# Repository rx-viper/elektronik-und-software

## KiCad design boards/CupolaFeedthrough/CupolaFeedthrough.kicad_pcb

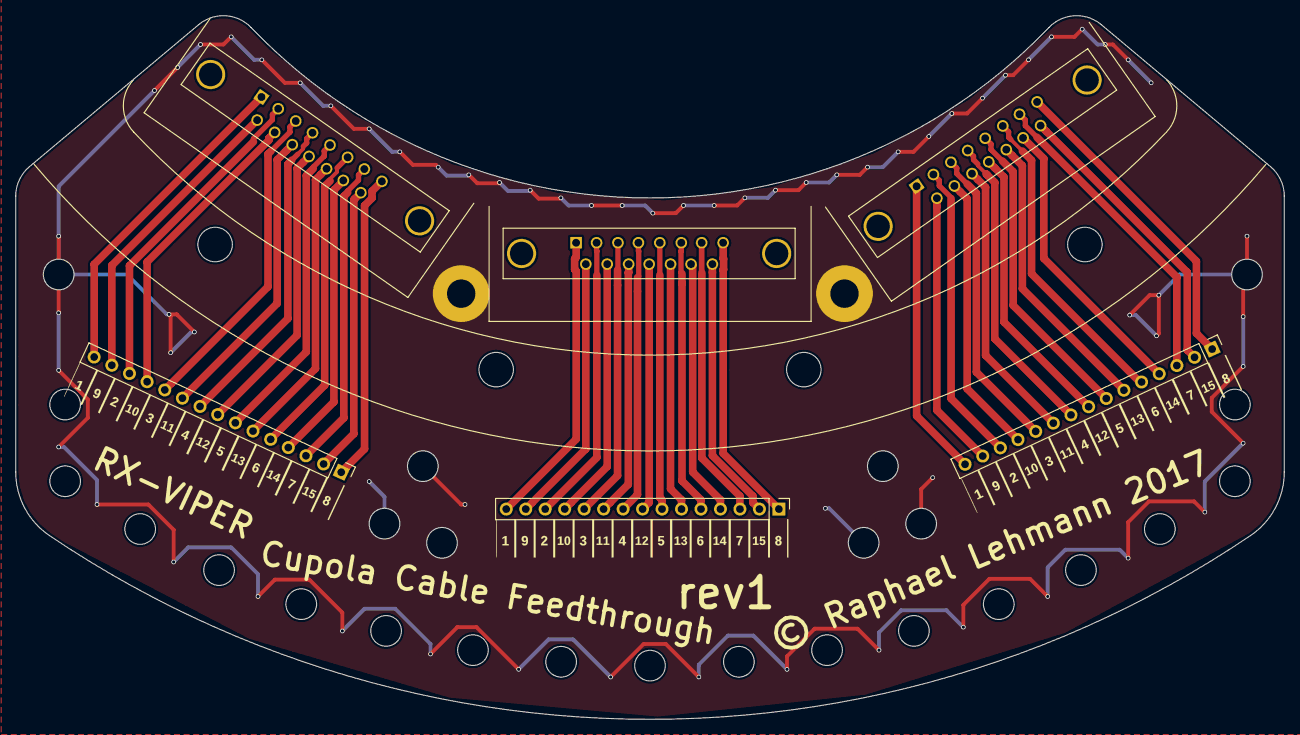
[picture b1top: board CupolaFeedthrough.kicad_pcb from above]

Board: 2 copper layers, 165.5 x 91.8 mm, 16 parts (0 on the bottom side), 46 nets.

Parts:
J101, J102, J103: CONN_01X15; Pin_Header_Straight_1x15_Pitch2.54mm
J104, J105, J106: DB15_FEMALE; DB15MD
J107, J108, J109, J110, J120, J121, J130, J131: GND; MountingHole_4mm
J136, J136#2: GND; MountingHole_3.7mm_Pad

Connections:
GND: J107.1, J108.1, J109.1, J110.1, J120.1, J121.1, J130.1, J131.1, J136.1, J136#2.1
unnamed: J101.1, J104.8
unnamed: J101.2, J104.15
unnamed: J101.3, J104.7
unnamed: J101.4, J104.14
unnamed: J101.5, J104.6
unnamed: J101.6, J104.13
unnamed: J101.7, J104.5
unnamed: J101.8, J104.12
unnamed: J101.9, J104.4
unnamed: J101.10, J104.11
unnamed: J101.11, J104.3
unnamed: J101.12, J104.10
unnamed: J101.13, J104.2
unnamed: J101.14, J104.9
unnamed: J101.15, J104.1
unnamed: J102.1, J105.8
unnamed: J102.2, J105.15
unnamed: J102.3, J105.7
unnamed: J102.4, J105.14
unnamed: J102.5, J105.6
unnamed: J102.6, J105.13
unnamed: J102.7, J105.5
unnamed: J102.8, J105.12
unnamed: J102.9, J105.4
unnamed: J102.10, J105.11
unnamed: J102.11, J105.3
unnamed: J102.12, J105.10
unnamed: J102.13, J105.2
unnamed: J102.14, J105.9
unnamed: J102.15, J105.1
unnamed: J103.1, J106.8
unnamed: J103.2, J106.15
unnamed: J103.3, J106.7
unnamed: J103.4, J106.14
unnamed: J103.5, J106.6
unnamed: J103.6, J106.13
unnamed: J103.7, J106.5
unnamed: J103.8, J106.12
unnamed: J103.9, J106.4
unnamed: J103.10, J106.11
unnamed: J103.11, J106.3
unnamed: J103.12, J106.10
unnamed: J103.13, J106.2
unnamed: J103.14, J106.9
unnamed: J103.15, J106.1

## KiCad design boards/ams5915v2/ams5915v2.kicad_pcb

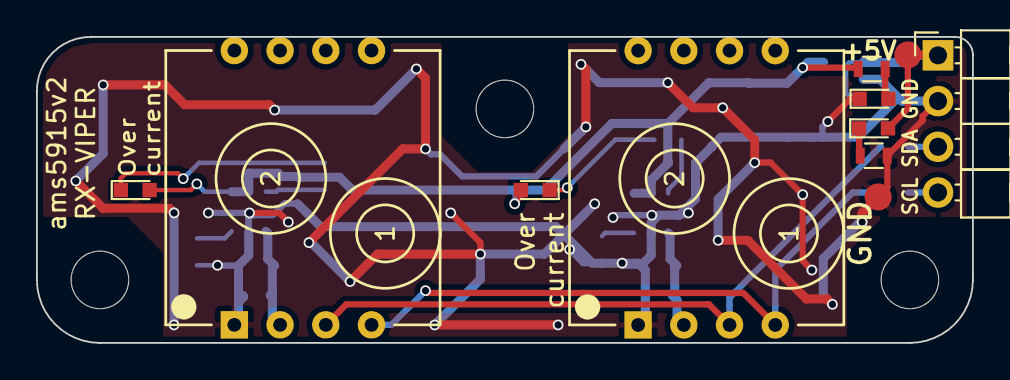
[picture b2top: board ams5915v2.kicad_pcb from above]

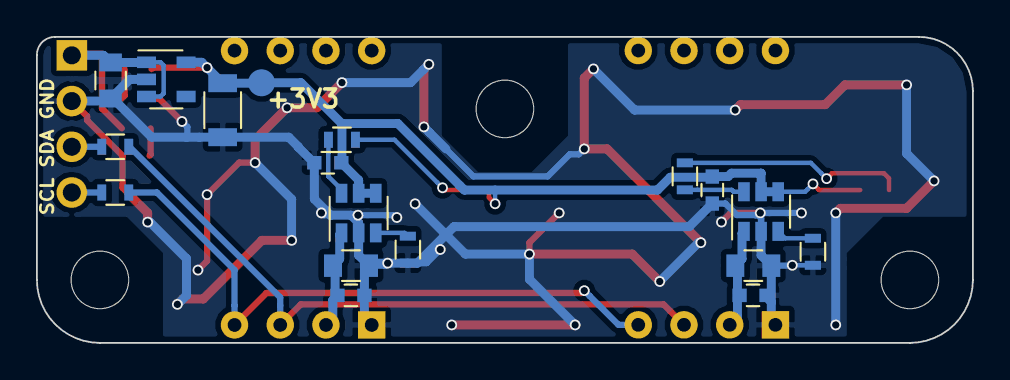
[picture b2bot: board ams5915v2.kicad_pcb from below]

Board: 2 copper layers, 52.0 x 17.0 mm, 29 parts (18 on the bottom side), 17 nets.

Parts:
C1, C7, C8: 1u; C_0805
C2: 10u; C_1206
C3, C4, C5, C6: 100n; C_0603
D1: LED_5v; LED_0603
D2: LED_3v3; LED_0603
D3: LED_P1; LED_0603
D4: LED_P2; LED_0603
J1: Conn_01x04; Pin_Header_Angled_1x04_Pitch2.54mm
R1, R2: 100; R_0603
R3: 4k7; R_0603
R4, R6, R8: 2k7; R_0603
R5, R7: 400k; R_0603
TP1: 5v; Measurement_Point_Round-SMD-Pad_Small
TP2: GND; Measurement_Point_Round-SMD-Pad_Small
TP3: 3v3; Measurement_Point_Round-SMD-Pad_Small
U1: TLV73333PDBVR; SOT-23-5
U2, U4: MAX4995A; SOT-23-6
U3, U5: AMS5915; AMS_5915-XXXX-D_differential_pressure_sensor

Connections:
+5V: C1.1, D1.2, J1.1, TP1.1, U1.1, U1.3
/3v3: C2.1, C3.1, C5.1, D3.2, D4.2, R4.1, TP3.1, U1.5, U2.4, U2.5, U4.4, U4.5
/SCL: J1.4, R1.1
/SDA: J1.3, R2.1
GND: C1.2, C2.2, C3.2, C4.2, C5.2, C6.2, C7.2, C8.2, D2.1, J1.2, R3.2, R5.1, R7.1, TP2.1, U1.2, U2.2, U3.1, U4.2, U5.1
unnamed: C4.1, C7.1, U2.1, U3.2
unnamed: C6.1, C8.1, U4.1, U5.2
unnamed: D1.1, R3.1
unnamed: D2.2, R4.2
unnamed: D3.1, R6.1
unnamed: D4.1, R8.1
unnamed: R1.2, U3.4, U5.4
unnamed: R2.2, U3.3, U5.3
unnamed: R5.2, U2.3
unnamed: R6.2, U2.6
unnamed: R7.2, U4.3
unnamed: R8.2, U4.6

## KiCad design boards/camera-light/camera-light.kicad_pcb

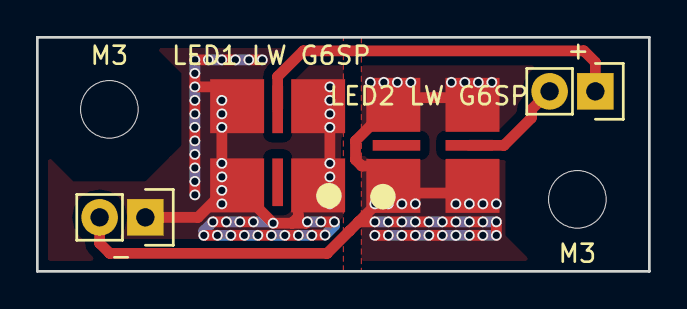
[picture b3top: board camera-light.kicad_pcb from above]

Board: 2 copper layers, 34.0 x 13.0 mm, 6 parts (0 on the bottom side), 4 nets.

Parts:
+: CONN_01X02; Pin_Header_Straight_1x02
-: CONN_01X02; Pin_Header_Straight_1x02
LED1 LW G6SP, LED2 LW G6SP: LED; LED_LW_G6SP
M3, M3#2: MountingHole_3.2mm_M3

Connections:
unnamed: +.1, LED1 LW G6SP.1
unnamed: -.1, LED1 LW G6SP.2, LED1 LW G6SP.~
unnamed: +.2, LED2 LW G6SP.1
unnamed: -.2, LED2 LW G6SP.2, LED2 LW G6SP.~

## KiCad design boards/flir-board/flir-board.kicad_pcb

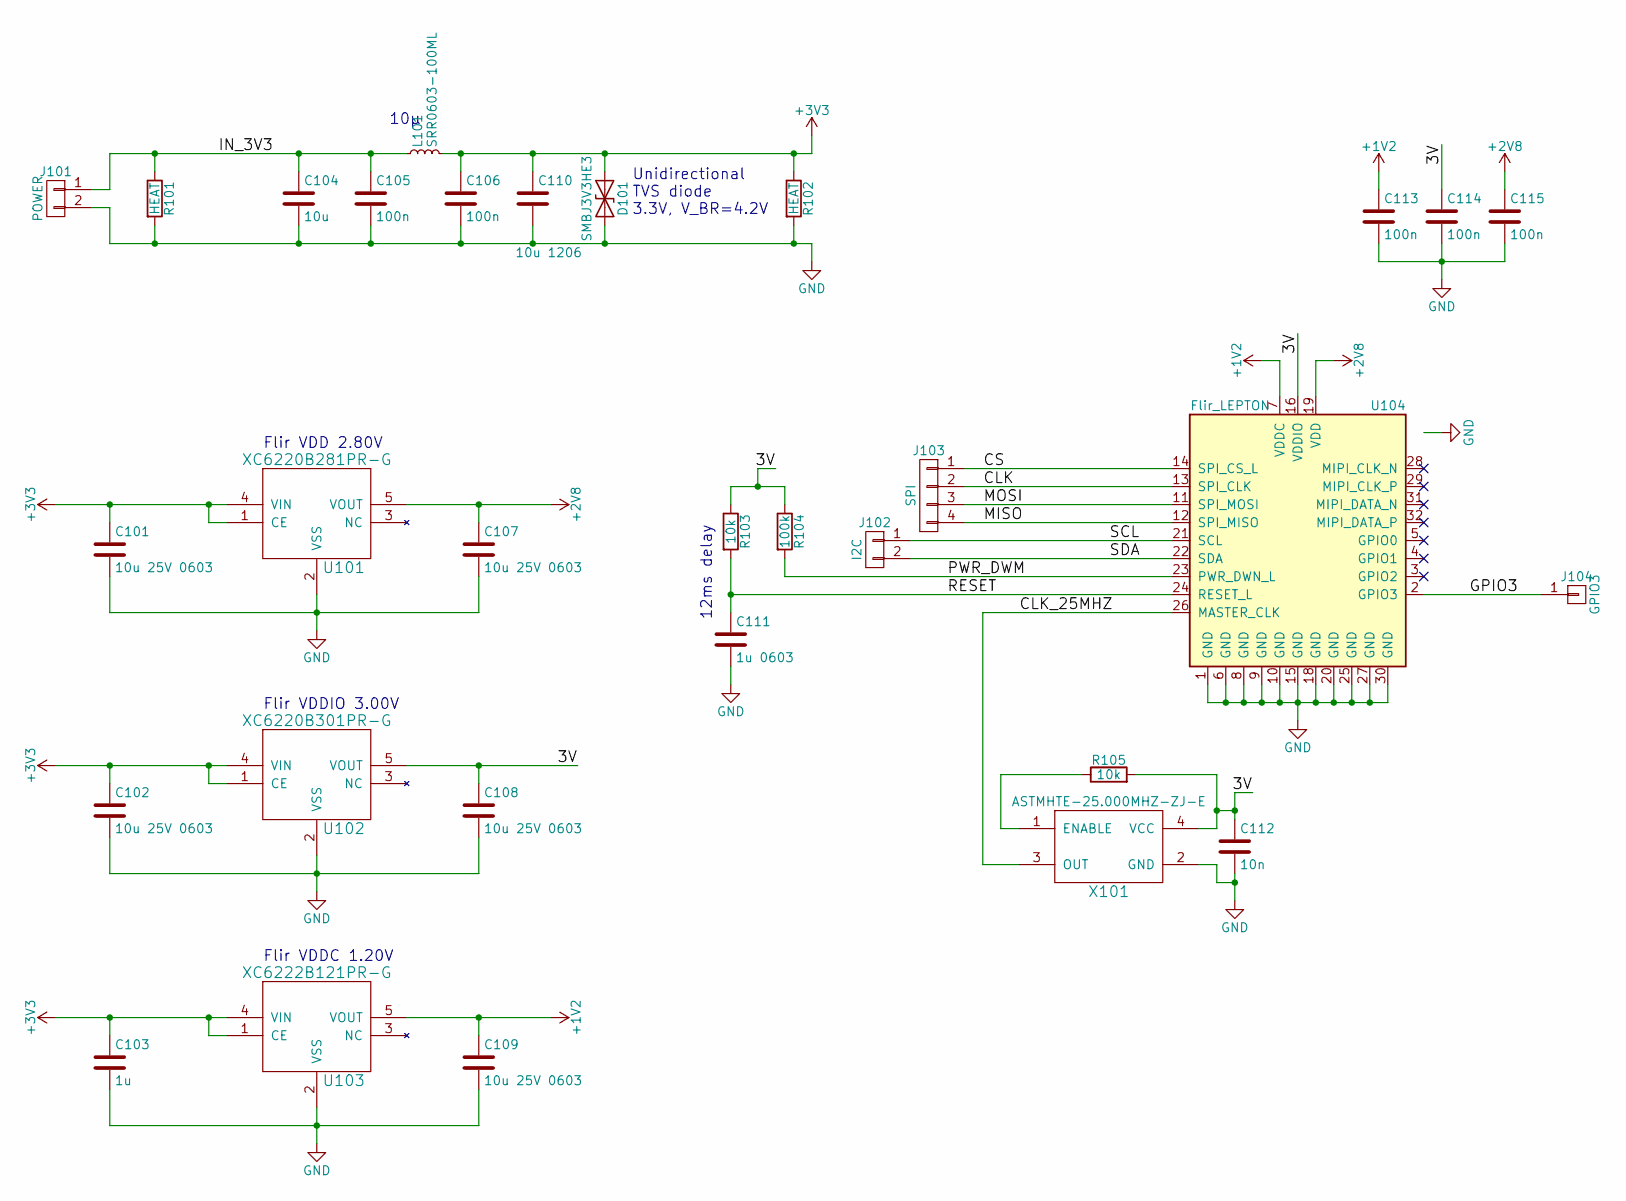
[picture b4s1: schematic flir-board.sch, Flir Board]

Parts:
C101, C102, C107, C108, C109: 10u 25V 0603; C_0603
C103: 1u; C_0603
C104: 10u; C_0805
C105, C106, C113, C114, C115: 100n; C_0603
C110: 10u 1206; C_1206
C111: 1u 0603; C_0603
C112: 10n; C_0603
D101: SMBJ3V3HE3; D_SMB_Standard
J101: POWER; Pin_Header_Straight_1x02_Pitch2.54mm
J102: I2C; Pin_Header_Straight_1x02_Pitch2.54mm
J103: SPI; Pin_Header_Straight_1x04_Pitch2.54mm
J104: GPIO3; Pin_Header_Straight_1x01_Pitch2.54mm
L101: SRR0603-100ML; L_7.3x7.3_H3.5
R101, R102: HEAT; R_1206
R103, R105: 10k; R_0603
R104: 100k; R_0603
U101: XC6220B281PR-G; SOT89-5_Housing
U102: XC6220B301PR-G; SOT89-5_Housing
U103: XC6222B121PR-G; SOT89-5_Housing
U104: Flir_LEPTON; Molex_105028-1001
X101: ASTMHTE-25.000MHZ-ZJ-E; ASTMHTE

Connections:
+1V2: C109.1, C113.1, U103.5 (VOUT), U104.7 (VDDC)
+2V8: C107.1, C115.1, U101.5 (VOUT), U104.19 (VDD)
+3V3: C101.1, C102.1, C103.1, C106.1, C110.1, D101.1 (A1), L101.2, R102.1, U101.1 (CE), U101.4 (VIN), U102.1 (CE), U102.4 (VIN), U103.1 (CE), U103.4 (VIN)
/3V: C108.1, C112.1, C114.1, R103.1, R104.1, R105.2, U102.5 (VOUT), U104.16 (VDDIO), X101.4 (VCC)
/CLK: J103.2, U104.13 (SPI_CLK)
/CLK_25MHZ: U104.26 (MASTER_CLK), X101.3 (OUT)
/CS: J103.1, U104.14 (SPI_CS_L)
/GPIO3: J104.1, U104.2 (GPIO3)
/IN_3V3: C104.1, C105.1, J101.1, L101.1, R101.1
/MISO: J103.4, U104.12 (SPI_MISO)
/MOSI: J103.3, U104.11 (SPI_MOSI)
/PWR_DWM: R104.2, U104.23 (PWR_DWN_L)
/RESET: C111.1, R103.2, U104.24 (RESET_L)
/SCL: J102.1, U104.21 (SCL)
/SDA: J102.2, U104.22 (SDA)
GND: C101.2, C102.2, C103.2, C104.2, C105.2, C106.2, C107.2, C108.2, C109.2, C110.2, C111.2, C112.2, C113.2, C114.2, C115.2, D101.2 (A2), J101.2, R101.2, R102.2, U101.2 (VSS), U102.2 (VSS), U103.2 (VSS), U104.1 (GND), U104.6 (GND), U104.8 (GND), U104.9 (GND), U104.10 (GND), U104.15 (GND), U104.18 (GND), U104.20 (GND), U104.25 (GND), U104.27 (GND), U104.30 (GND), U104.33, X101.2 (GND)
unnamed: R105.1, X101.1 (ENABLE)

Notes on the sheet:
Flir VDDIO 3.00V
Flir VDD 2.80V
Flir VDDC 1.20V
12ms delay
10µ
Unidirectional TVS diode 3.3V, V_BR=4.2V

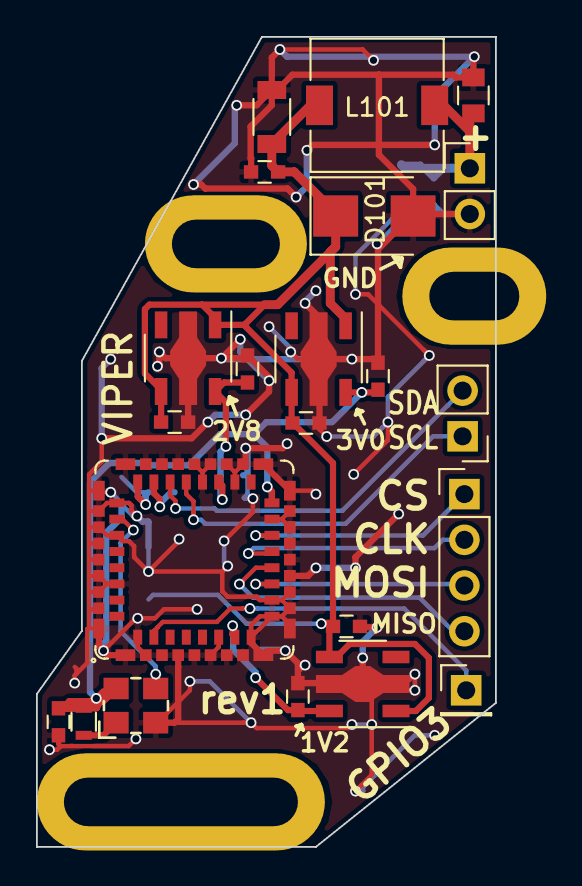
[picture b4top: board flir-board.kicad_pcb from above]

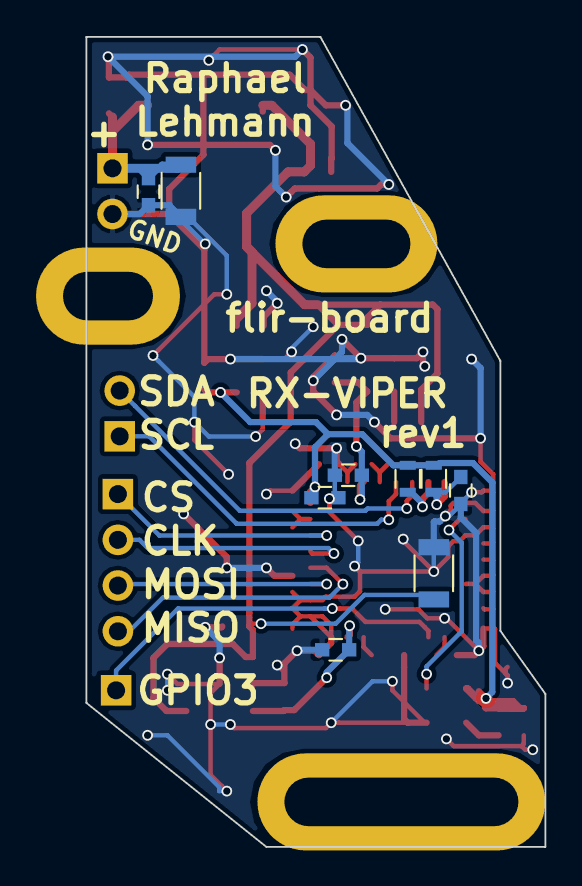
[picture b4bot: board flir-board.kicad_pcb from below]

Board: 2 copper layers, 25.5 x 45.0 mm, 31 parts (9 on the bottom side), 17 nets.

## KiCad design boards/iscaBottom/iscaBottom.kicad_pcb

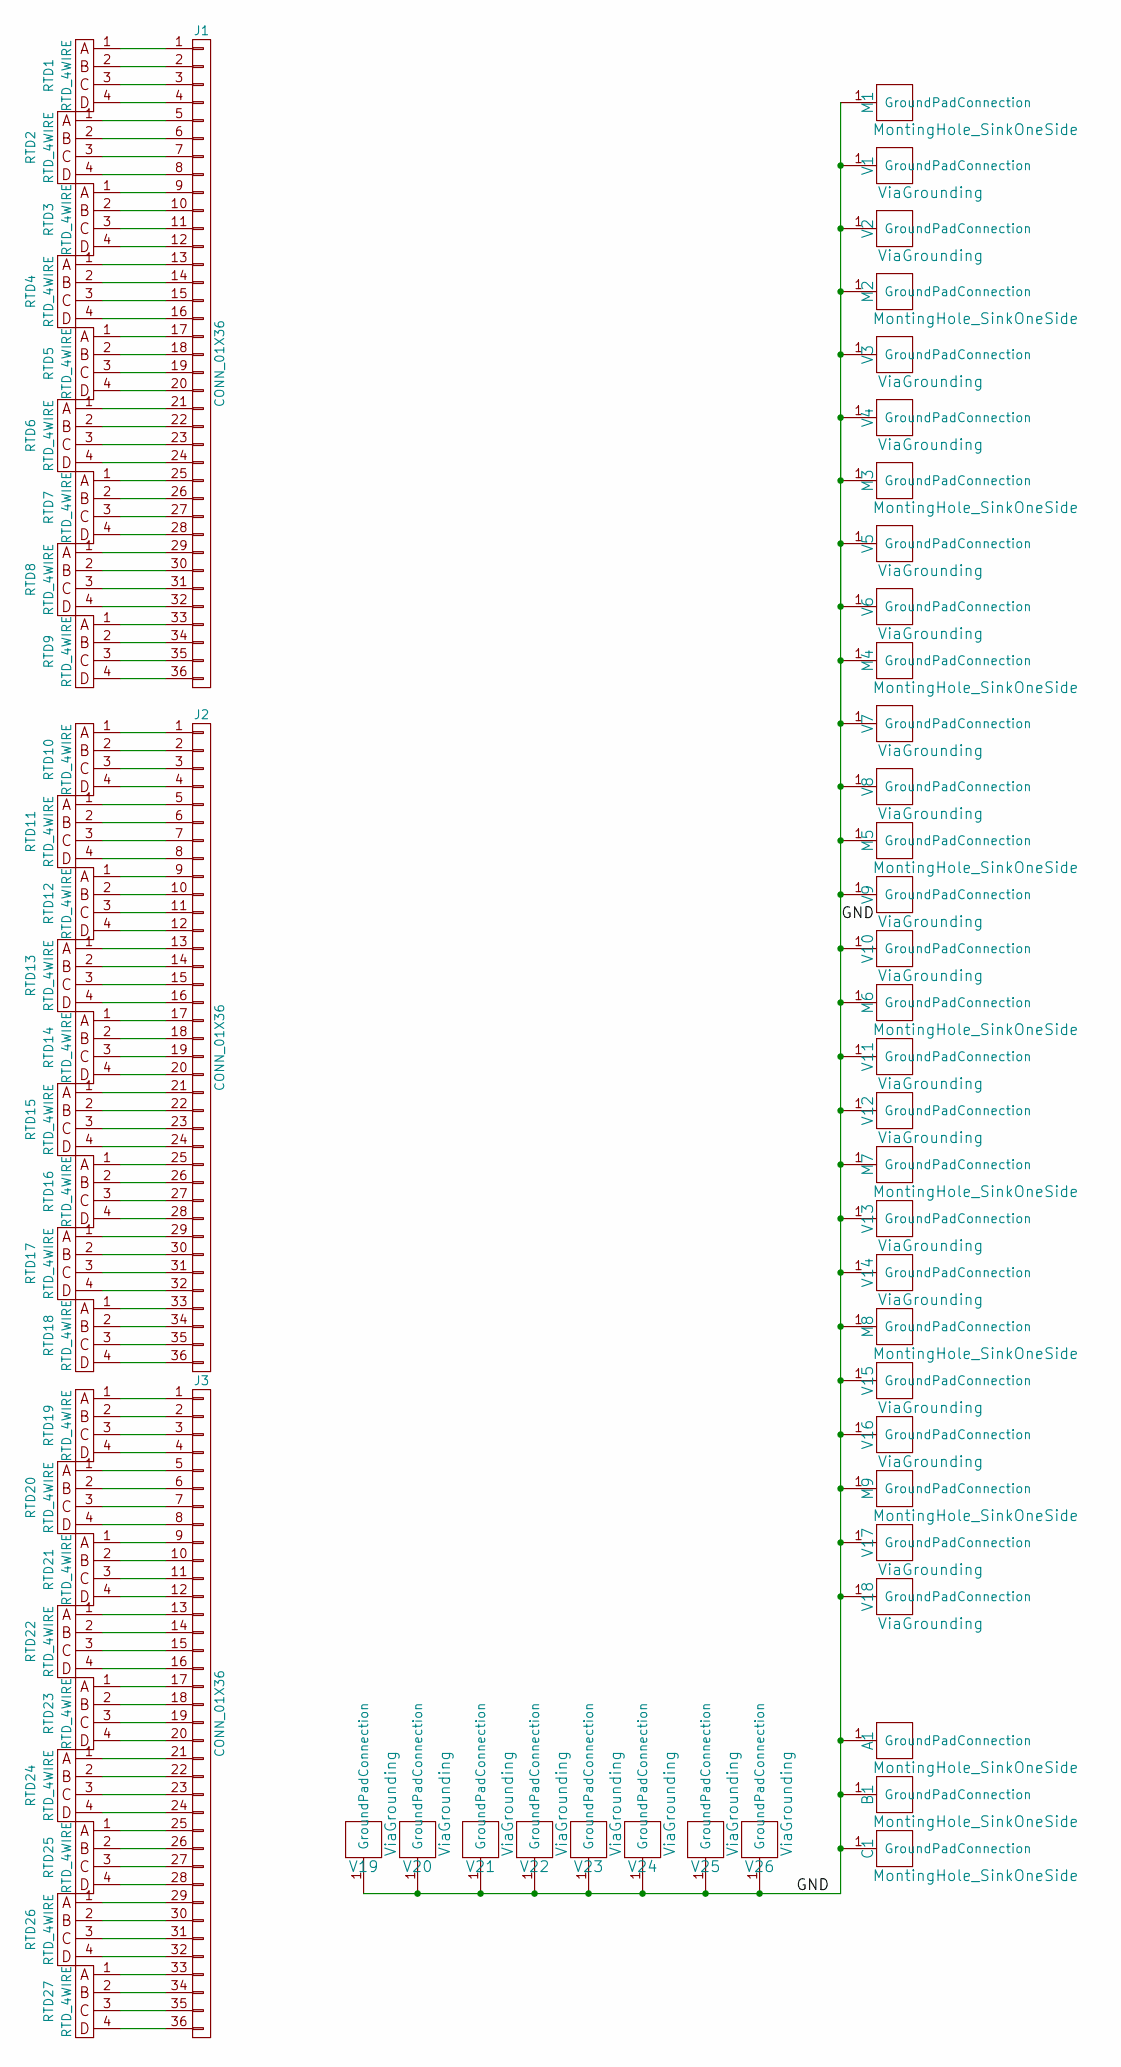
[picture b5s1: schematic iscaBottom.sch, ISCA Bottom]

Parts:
A1: MontingHole_SinkOneSide; MountingHoleM2_2.2mm_oneSided
B1: MontingHole_SinkOneSide; MountingHoleM2_2.2mm_oneSided
C1: MontingHole_SinkOneSide; MountingHoleM2_2.2mm_oneSided
J1, J2, J3: CONN_01X36; 36wire014mm2
M1, M2, M3, M4, M5, M6, M7, M8, M9: MontingHole_SinkOneSide; MountingHoleM2_2.2mm_oneSided
RTD1, RTD2, RTD3, RTD4, RTD5, RTD6, RTD7, RTD8, RTD9, RTD10, RTD11, RTD12, RTD13, RTD14, RTD19, RTD20, RTD21, RTD22, RTD23, RTD24, RTD25, RTD26, RTD27: RTD_4WIRE; 4wire_SMDsolder
RTD15, RTD16, RTD17, RTD18: RTD_4WIRE; 4wire_SMDsolder_reverse
V1, V2, V3, V4, V5, V6, V7, V8, V9, V10, V11, V12, V13, V14, V15, V16, V17, V18, V19, V20, V21, V22, V23, V24, V25, V26: ViaGrounding; GroundingVia

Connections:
/GND: A1.1, B1.1, C1.1, M1.1, M2.1, M3.1, M4.1, M5.1, M6.1, M7.1, M8.1, M9.1, V1.1, V2.1, V3.1, V4.1, V5.1, V6.1, V7.1, V8.1, V9.1, V10.1, V11.1, V12.1, V13.1, V14.1, V15.1, V16.1, V17.1, V18.1, V19.1, V20.1, V21.1, V22.1, V23.1, V24.1, V25.1, V26.1
unnamed: J1.1, RTD1.1
unnamed: J1.2, RTD1.2
unnamed: J1.3, RTD1.3
unnamed: J1.4, RTD1.4
unnamed: J1.5, RTD2.1
unnamed: J1.6, RTD2.2
unnamed: J1.7, RTD2.3
unnamed: J1.8, RTD2.4
unnamed: J1.9, RTD3.1
unnamed: J1.10, RTD3.2
unnamed: J1.11, RTD3.3
unnamed: J1.12, RTD3.4
unnamed: J1.13, RTD4.1
unnamed: J1.14, RTD4.2
unnamed: J1.15, RTD4.3
unnamed: J1.16, RTD4.4
unnamed: J1.17, RTD5.1
unnamed: J1.18, RTD5.2
unnamed: J1.19, RTD5.3
unnamed: J1.20, RTD5.4
unnamed: J1.21, RTD6.1
unnamed: J1.22, RTD6.2
unnamed: J1.23, RTD6.3
unnamed: J1.24, RTD6.4
unnamed: J1.25, RTD7.1
unnamed: J1.26, RTD7.2
unnamed: J1.27, RTD7.3
unnamed: J1.28, RTD7.4
unnamed: J1.29, RTD8.1
unnamed: J1.30, RTD8.2
unnamed: J1.31, RTD8.3
unnamed: J1.32, RTD8.4
unnamed: J1.33, RTD9.1
unnamed: J1.34, RTD9.2
unnamed: J1.35, RTD9.3
unnamed: J1.36, RTD9.4
unnamed: J2.1, RTD10.1
unnamed: J2.2, RTD10.2
unnamed: J2.3, RTD10.3
unnamed: J2.4, RTD10.4
unnamed: J2.5, RTD11.1
unnamed: J2.6, RTD11.2
unnamed: J2.7, RTD11.3
unnamed: J2.8, RTD11.4
unnamed: J2.9, RTD12.1
unnamed: J2.10, RTD12.2
unnamed: J2.11, RTD12.3
unnamed: J2.12, RTD12.4
unnamed: J2.13, RTD13.1
unnamed: J2.14, RTD13.2
unnamed: J2.15, RTD13.3
unnamed: J2.16, RTD13.4
unnamed: J2.17, RTD14.1
unnamed: J2.18, RTD14.2
unnamed: J2.19, RTD14.3
unnamed: J2.20, RTD14.4
unnamed: J2.21, RTD15.1
unnamed: J2.22, RTD15.2
unnamed: J2.23, RTD15.3
unnamed: J2.24, RTD15.4
unnamed: J2.25, RTD16.1
unnamed: J2.26, RTD16.2
unnamed: J2.27, RTD16.3
unnamed: J2.28, RTD16.4
unnamed: J2.29, RTD17.1
unnamed: J2.30, RTD17.2
unnamed: J2.31, RTD17.3
unnamed: J2.32, RTD17.4
unnamed: J2.33, RTD18.1
unnamed: J2.34, RTD18.2
unnamed: J2.35, RTD18.3
unnamed: J2.36, RTD18.4
unnamed: J3.1, RTD19.1
unnamed: J3.2, RTD19.2
unnamed: J3.3, RTD19.3
unnamed: J3.4, RTD19.4
unnamed: J3.5, RTD20.1
unnamed: J3.6, RTD20.2
unnamed: J3.7, RTD20.3
unnamed: J3.8, RTD20.4
unnamed: J3.9, RTD21.1
unnamed: J3.10, RTD21.2
unnamed: J3.11, RTD21.3
unnamed: J3.12, RTD21.4
unnamed: J3.13, RTD22.1
unnamed: J3.14, RTD22.2
unnamed: J3.15, RTD22.3
unnamed: J3.16, RTD22.4
unnamed: J3.17, RTD23.1
unnamed: J3.18, RTD23.2
unnamed: J3.19, RTD23.3
unnamed: J3.20, RTD23.4
unnamed: J3.21, RTD24.1
unnamed: J3.22, RTD24.2
unnamed: J3.23, RTD24.3
unnamed: J3.24, RTD24.4
unnamed: J3.25, RTD25.1
unnamed: J3.26, RTD25.2
unnamed: J3.27, RTD25.3
unnamed: J3.28, RTD25.4
unnamed: J3.29, RTD26.1
unnamed: J3.30, RTD26.2
unnamed: J3.31, RTD26.3
unnamed: J3.32, RTD26.4
unnamed: J3.33, RTD27.1
unnamed: J3.34, RTD27.2
unnamed: J3.35, RTD27.3
unnamed: J3.36, RTD27.4

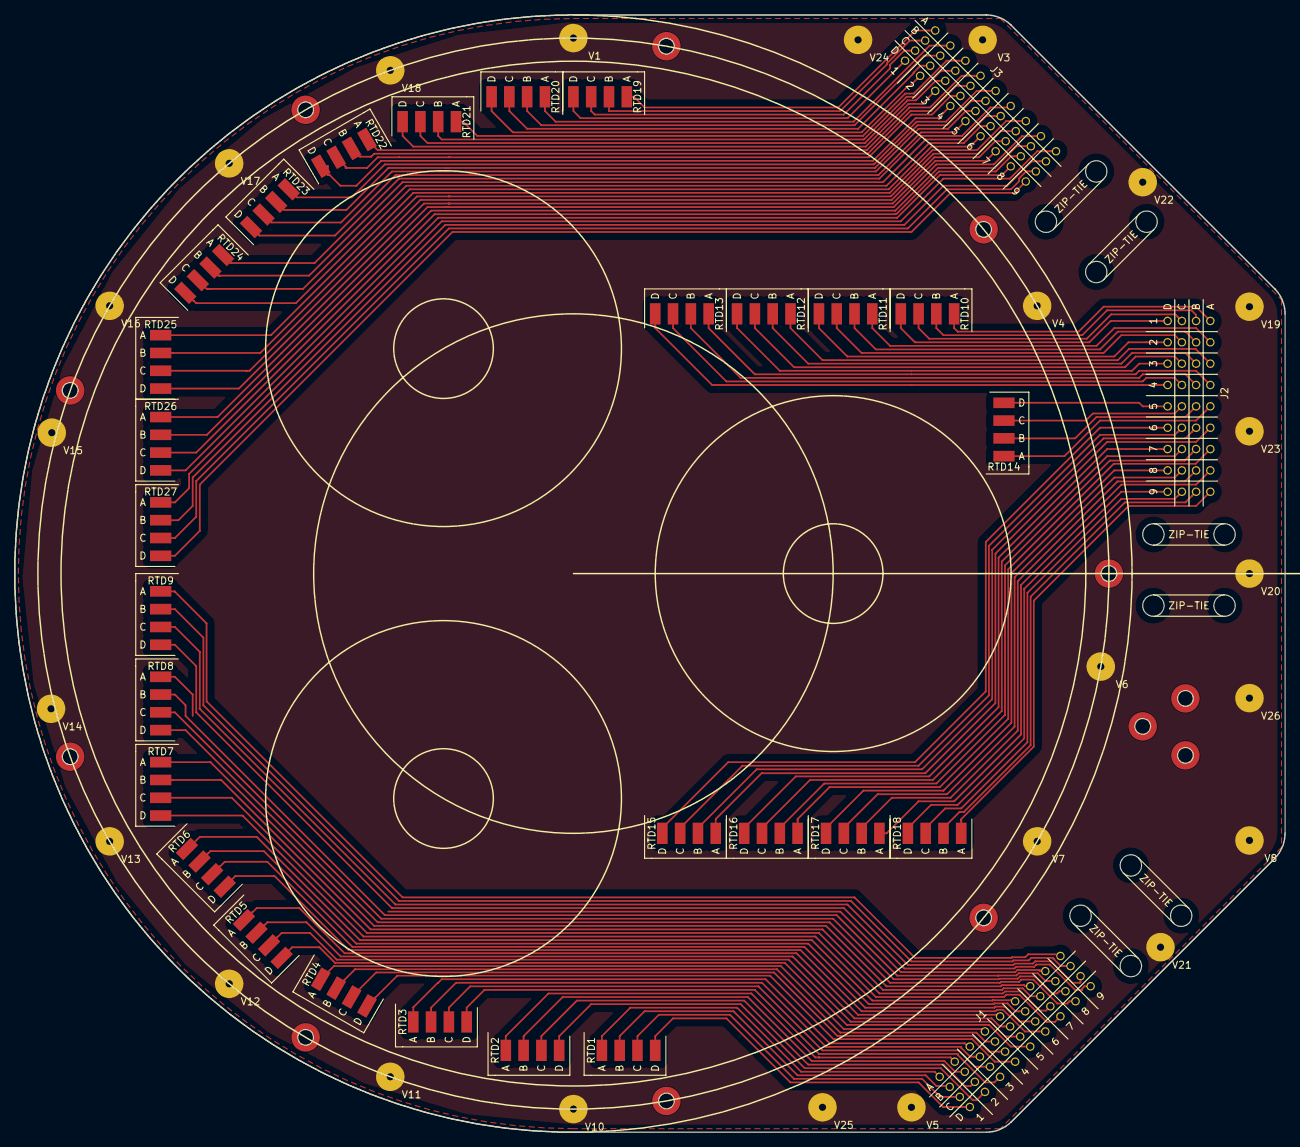
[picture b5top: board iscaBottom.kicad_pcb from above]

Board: 2 copper layers, 178.5 x 157.0 mm, 66 parts (0 on the bottom side), 109 nets.

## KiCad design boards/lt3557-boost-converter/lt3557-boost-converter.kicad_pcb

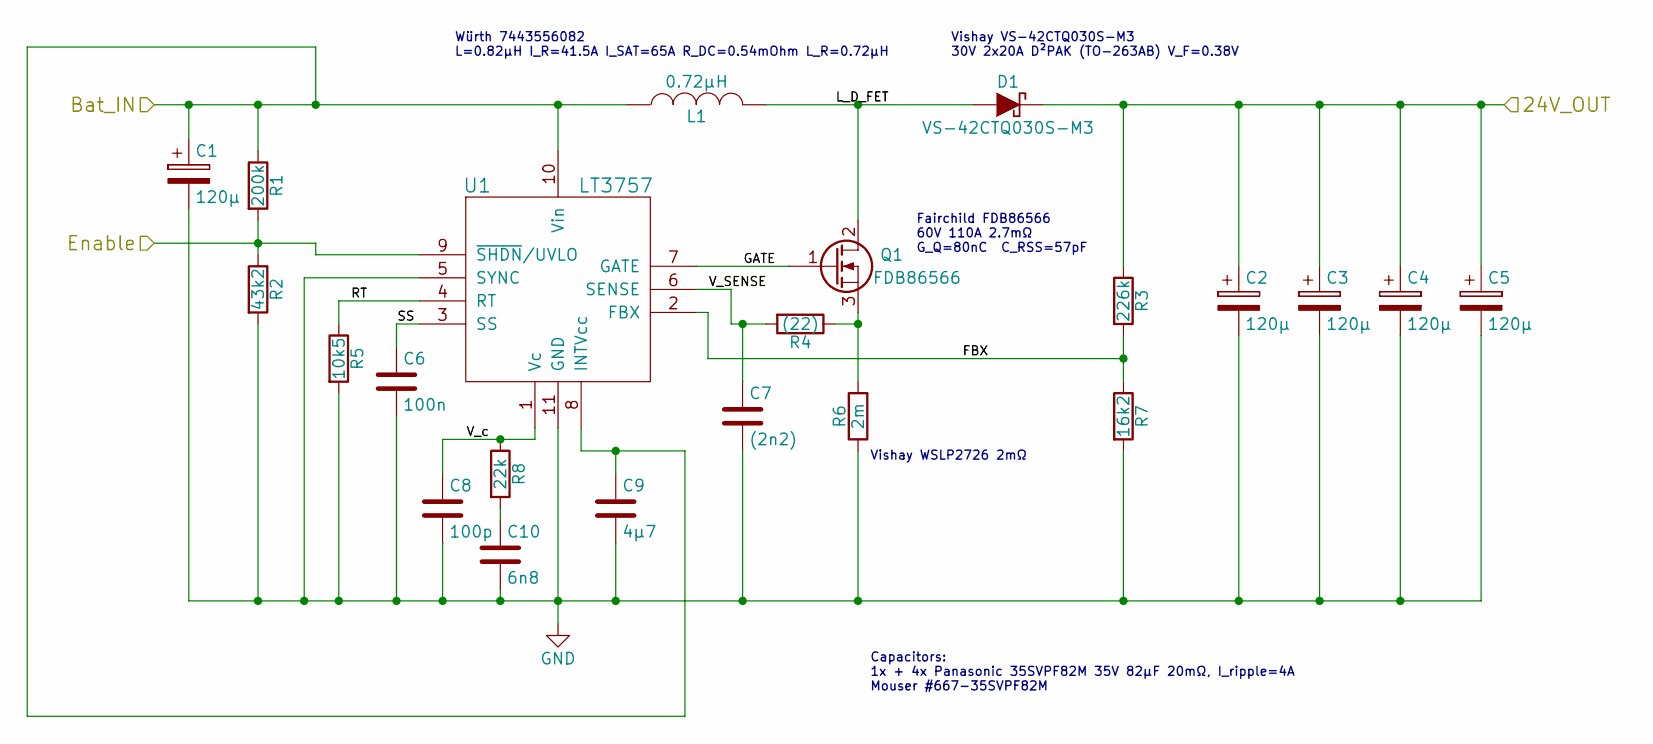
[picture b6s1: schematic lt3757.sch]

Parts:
C1, C2, C3, C4, C5: 120µ; c_elec_8x10.5
C6: 100n; C_0603
C7: (2n2); C_0603
C8: 100p; C_0603
C9: 4µ7; C_0805
C10: 6n8; C_0603
D1: VS-42CTQ030S-M3; DD-PAK_TO263_DualDiode_ThermalVias
L1: 0.72µH; Inductor_Wurth_HCI-1890
Q1: FDB86566; DD-PAK_TO263_DualDiode_ThermalVias
R1: 200k; R_0603
R2: 43k2; R_0603
R3: 226k; R_0603
R4: (22); R_0603
R5: 10k5; R_0603
R6: 2m; WSLP2726
R7: 16k2; R_0603
R8: 22k; R_0603
U1: LT3757; MSOP-10-1EP_3x3mm_Pitch0.5mm

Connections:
/LT3757/24V_OUT: C2.1, C3.1, C4.1, C5.1, D1.1 (K), R3.1; also elsewhere on the board
/LT3757/Bat_IN: C1.1, C9.1, L1.1, R1.1, U1.8 (INTVcc), U1.10 (Vin); also elsewhere on the board
/LT3757/Enable: R1.2, R2.1, U1.9 (~SHDN~/UVLO); also elsewhere on the board
/LT3757/FBX: R3.2, R7.1, U1.2 (FBX)
/LT3757/GATE: Q1.1 (G), U1.7 (GATE)
/LT3757/L_D_FET: D1.2 (A), L1.2, Q1.2 (D)
/LT3757/RT: R5.1, U1.4 (RT)
/LT3757/SS: C6.1, U1.3 (SS)
/LT3757/V_SENSE: C7.1, R4.2, U1.6 (SENSE)
/LT3757/V_c: C8.1, R8.1, U1.1 (Vc)
GND: C1.2, C2.2, C3.2, C4.2, C5.2, C6.2, C7.2, C8.2, C9.2, C10.2, R2.2, R5.2, R6.1, R7.2, U1.5 (SYNC), U1.11 (GND); also elsewhere on the board
unnamed: C10.1, R8.2
unnamed: Q1.3 (S), R4.1, R6.2

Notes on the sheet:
Würth 7443556082 L=0.82µH I_R=41.5A I_SAT=65A R_DC=0.54mOhm L_R=0.72µH
Vishay VS-42CTQ030S-M3 30V 2x20A D²PAK (TO-263AB) V_F=0.38V
Capacitors: 1x + 4x Panasonic 35SVPF82M 35V 82µF 20mΩ, I_ripple=4A Mouser #667-35SVPF82M
Vishay WSLP2726 2mΩ
Fairchild FDB86566 60V 110A 2.7mΩ G_Q=80nC C_RSS=57pF

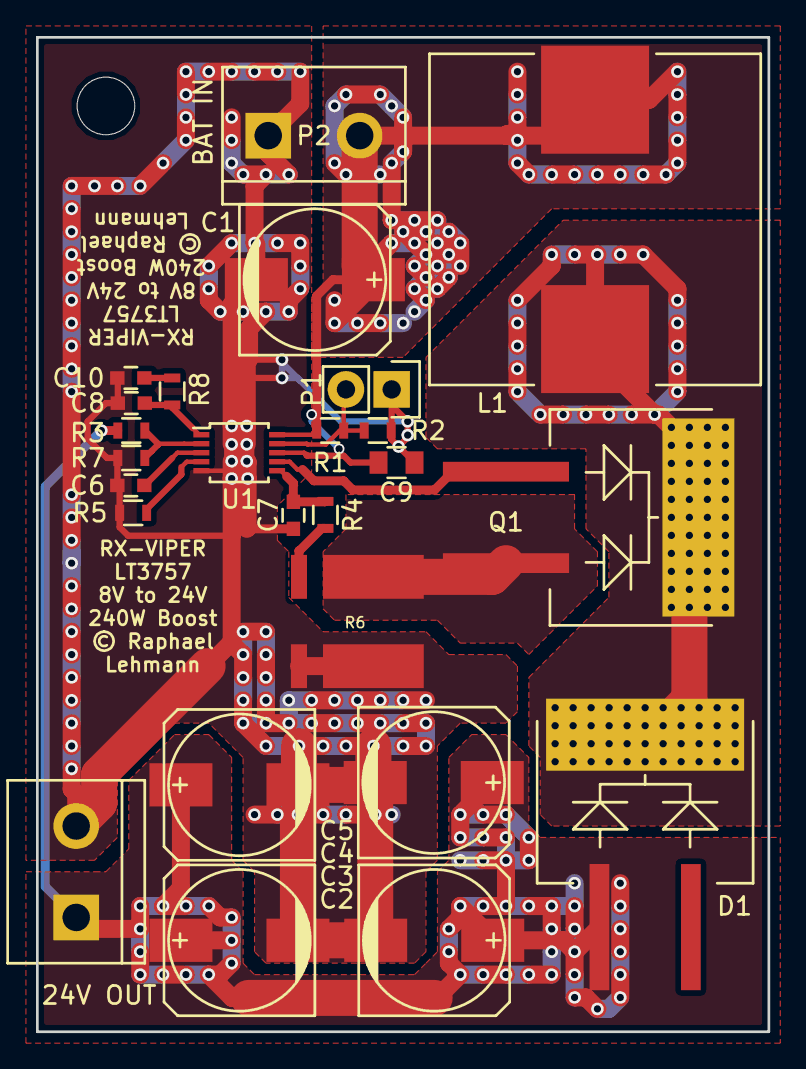
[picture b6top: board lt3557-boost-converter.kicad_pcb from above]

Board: 2 copper layers, 40.6 x 55.2 mm, 25 parts (0 on the bottom side), 13 nets.

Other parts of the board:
P1: Enable; Pin_Header_Straight_1x02
P2: BAT IN; bornier2
P3: 24V OUT; bornier2

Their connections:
/LT3757/24V_OUT: P3.1; also elsewhere on the board
/LT3757/Bat_IN: P2.2; also elsewhere on the board
/LT3757/Enable: P1.2; also elsewhere on the board
GND: P1.1, P2.1, P3.2; also elsewhere on the board

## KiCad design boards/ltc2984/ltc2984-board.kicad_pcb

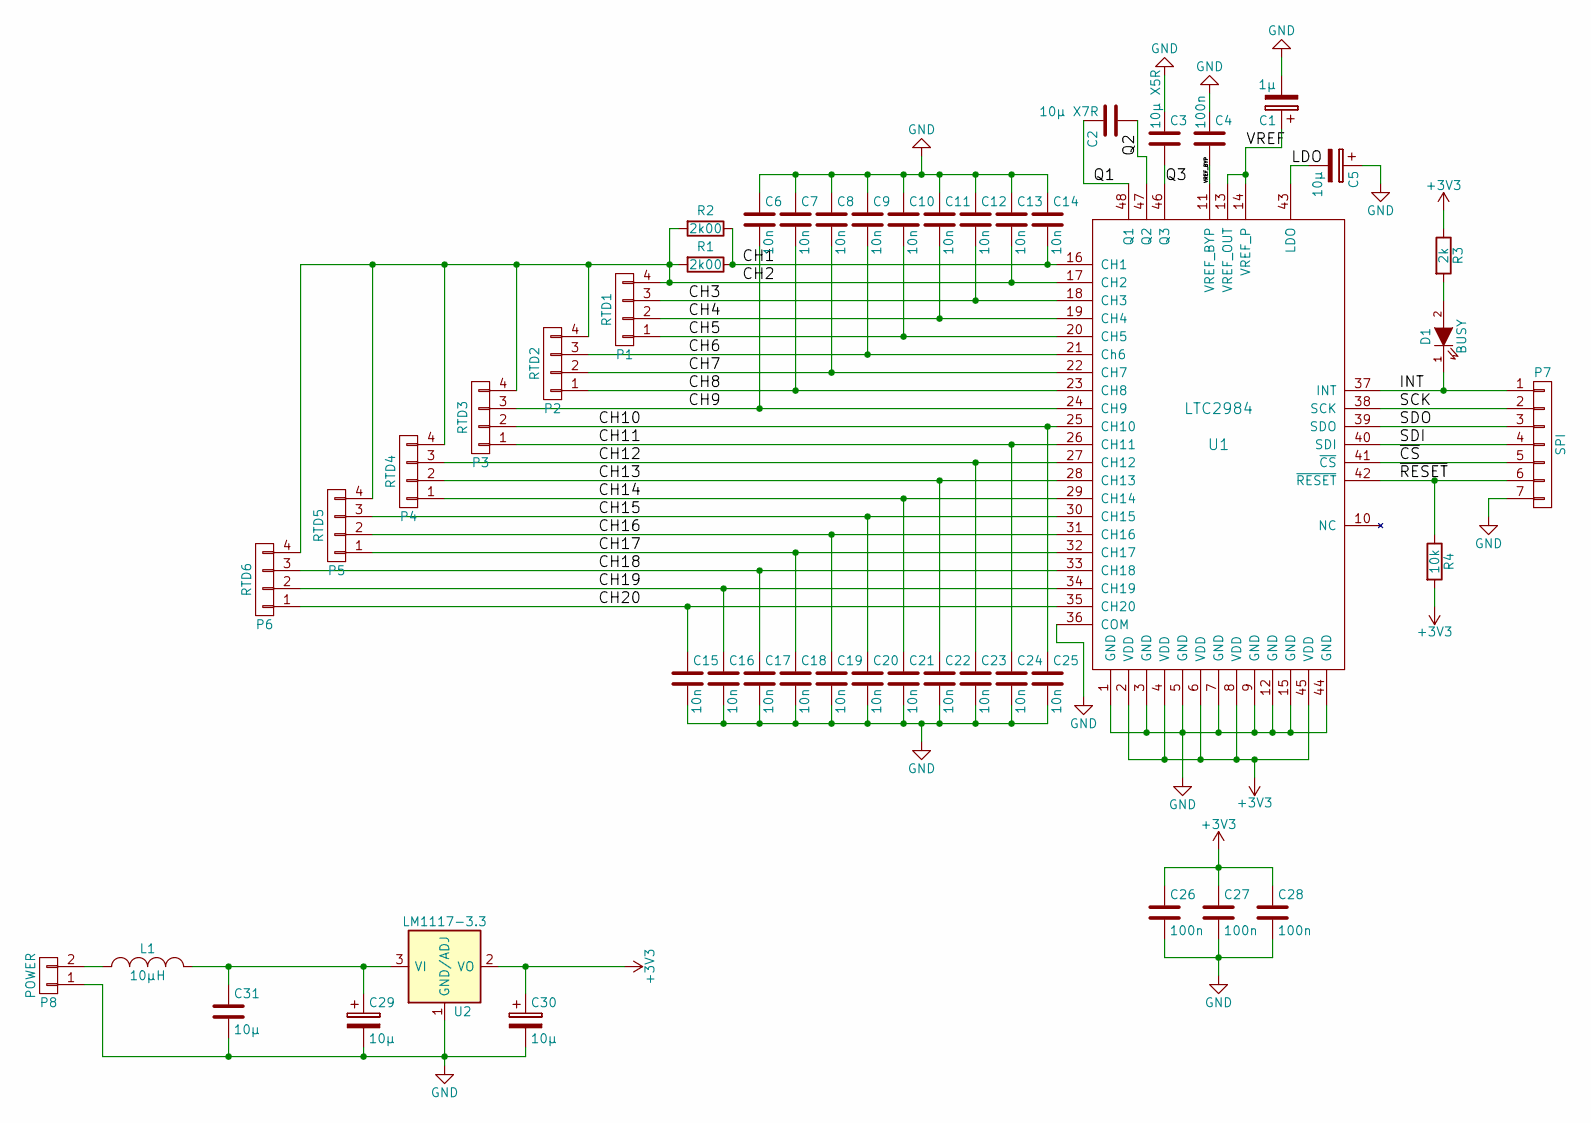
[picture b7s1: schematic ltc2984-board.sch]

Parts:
C1: 1µ; C_0805
C2: 10µ X7R; C_0805
C3: 10µ X5R; C_0805
C4, C26, C27, C28: 100n; C_0603
C5, C29, C30: 10µ; C_0805
C6, C7, C8, C9, C10, C11, C12, C13, C14, C15, C16, C17, C18, C19, C20, C21, C22, C23, C24, C25: 10n; C_0603
C31: 10µ; C_0603
D1: BUSY; LED_0603
L1: 10µH; R_0603
P1: RTD1; Pin_Header_Straight_1x04
P2: RTD2; Pin_Header_Straight_1x04
P3: RTD3; Pin_Header_Straight_1x04
P4: RTD4; Pin_Header_Straight_1x04
P5: RTD5; Pin_Header_Straight_1x04
P6: RTD6; Pin_Header_Straight_1x04
P7: SPI; Pin_Header_Straight_1x07
P8: POWER; Pin_Header_Straight_1x02
R1: 2k00; Resistor_Horizontal_RM7mm
R2: 2k00; R_1206
R3: 2k; R_0603
R4: 10k; R_0603
U1: LTC2984; LQFP-48_7x7mm_Pitch0.5mm
U2: LM1117-3.3; SOT-223

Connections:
+3V3: C26.1, C27.1, C28.1, C30.1, R3.1, R4.2, U1.2 (VDD), U1.4 (VDD), U1.6 (VDD), U1.8 (VDD), U1.45 (VDD), U2.2 (VO), U2.4 (VO)
/CH1: C14.2, R1.1, R2.1, U1.16 (CH1)
/CH2: C13.2, P1.4, P2.4, P3.4, P4.4, P5.4, P6.4, R1.2, R2.2, U1.17 (CH2)
/CH3: C12.2, P1.3, U1.18 (CH3)
/CH4: C11.2, P1.2, U1.19 (CH4)
/CH5: C10.2, P1.1, U1.20 (CH5)
/CH6: C9.2, P2.3, U1.21 (Ch6)
/CH7: C8.2, P2.2, U1.22 (CH7)
/CH8: C7.2, P2.1, U1.23 (CH8)
/CH9: C6.2, P3.3, U1.24 (CH9)
/CH10: C25.1, P3.2, U1.25 (CH10)
/CH11: C24.1, P3.1, U1.26 (CH11)
/CH12: C23.1, P4.3, U1.27 (CH12)
/CH13: C22.1, P4.2, U1.28 (CH13)
/CH14: C21.1, P4.1, U1.29 (CH14)
/CH15: C20.1, P5.3, U1.30 (CH15)
/CH16: C19.1, P5.2, U1.31 (CH16)
/CH17: C18.1, P5.1, U1.32 (CH17)
/CH18: C17.1, P6.3, U1.33 (CH18)
/CH19: C16.1, P6.2, U1.34 (CH19)
/CH20: C15.1, P6.1, U1.35 (CH20)
/INT: D1.1 (K), P7.1, U1.37 (INT)
/LDO: C5.2, U1.43 (LDO)
/Q1: C2.2, U1.48 (Q1)
/Q2: C2.1, U1.47 (Q2)
/Q3: C3.2, U1.46 (Q3)
/SCK: P7.2, U1.38 (SCK)
/SDI: P7.4, U1.40 (SDI)
/SDO: P7.3, U1.39 (SDO)
/VREF: C1.1, U1.13 (VREF_OUT), U1.14 (VREF_P)
/VREF_BYP: C4.2, U1.11 (VREF_BYP)
/~CS: P7.5, U1.41 (~CS)
/~RESET: P7.6, R4.1, U1.42 (~RESET)
GND: C1.2, C3.1, C4.1, C5.1, C6.1, C7.1, C8.1, C9.1, C10.1, C11.1, C12.1, C13.1, C14.1, C15.2, C16.2, C17.2, C18.2, C19.2, C20.2, C21.2, C22.2, C23.2, C24.2, C25.2, C26.2, C27.2, C28.2, C29.2, C30.2, C31.2, P7.7, P8.1, U1.1 (GND), U1.3 (GND), U1.5 (GND), U1.7 (GND), U1.9 (GND), U1.12 (GND), U1.15 (GND), U1.36 (COM), U1.44 (GND), U2.1 (GND/ADJ)
unnamed: C29.1, C31.1, L1.2, U2.3 (VI)
unnamed: D1.2 (A), R3.2
unnamed: L1.1, P8.2

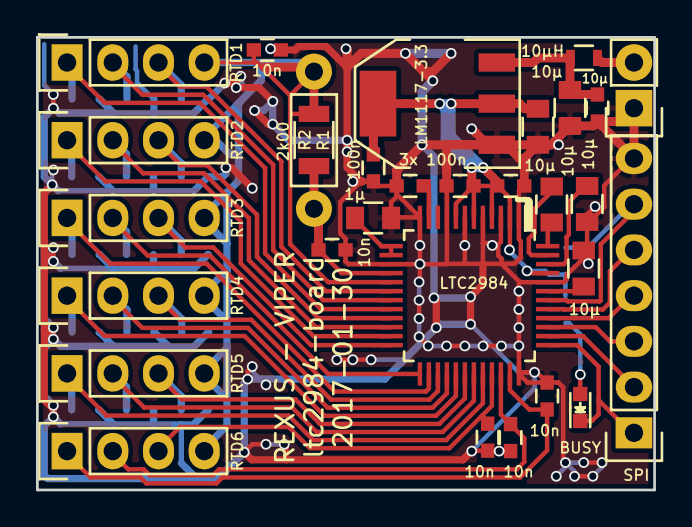
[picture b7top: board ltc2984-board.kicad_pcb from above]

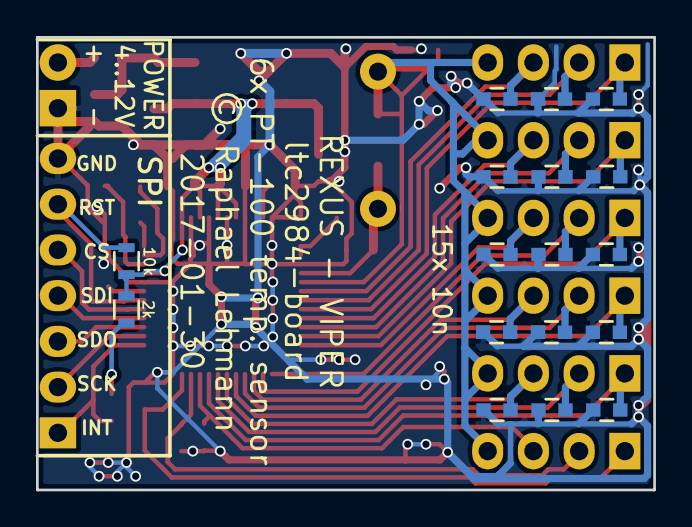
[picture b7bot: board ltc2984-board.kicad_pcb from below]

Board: 2 copper layers, 34.3 x 25.1 mm, 47 parts (17 on the bottom side), 37 nets.

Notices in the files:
boards/CupolaFeedthrough/CupolaFeedthrough.kicad_pcb:
© Raphael Lehmann 2017
boards/camera-light/camera-light.kicad_pcb:
© Leonard Rapp
boards/iscaBottom/iscaBottom.kicad_pcb:
©rchojetzki
boards/lt3557-boost-converter/lt3557-boost-converter.kicad_pcb:
© Raphael
